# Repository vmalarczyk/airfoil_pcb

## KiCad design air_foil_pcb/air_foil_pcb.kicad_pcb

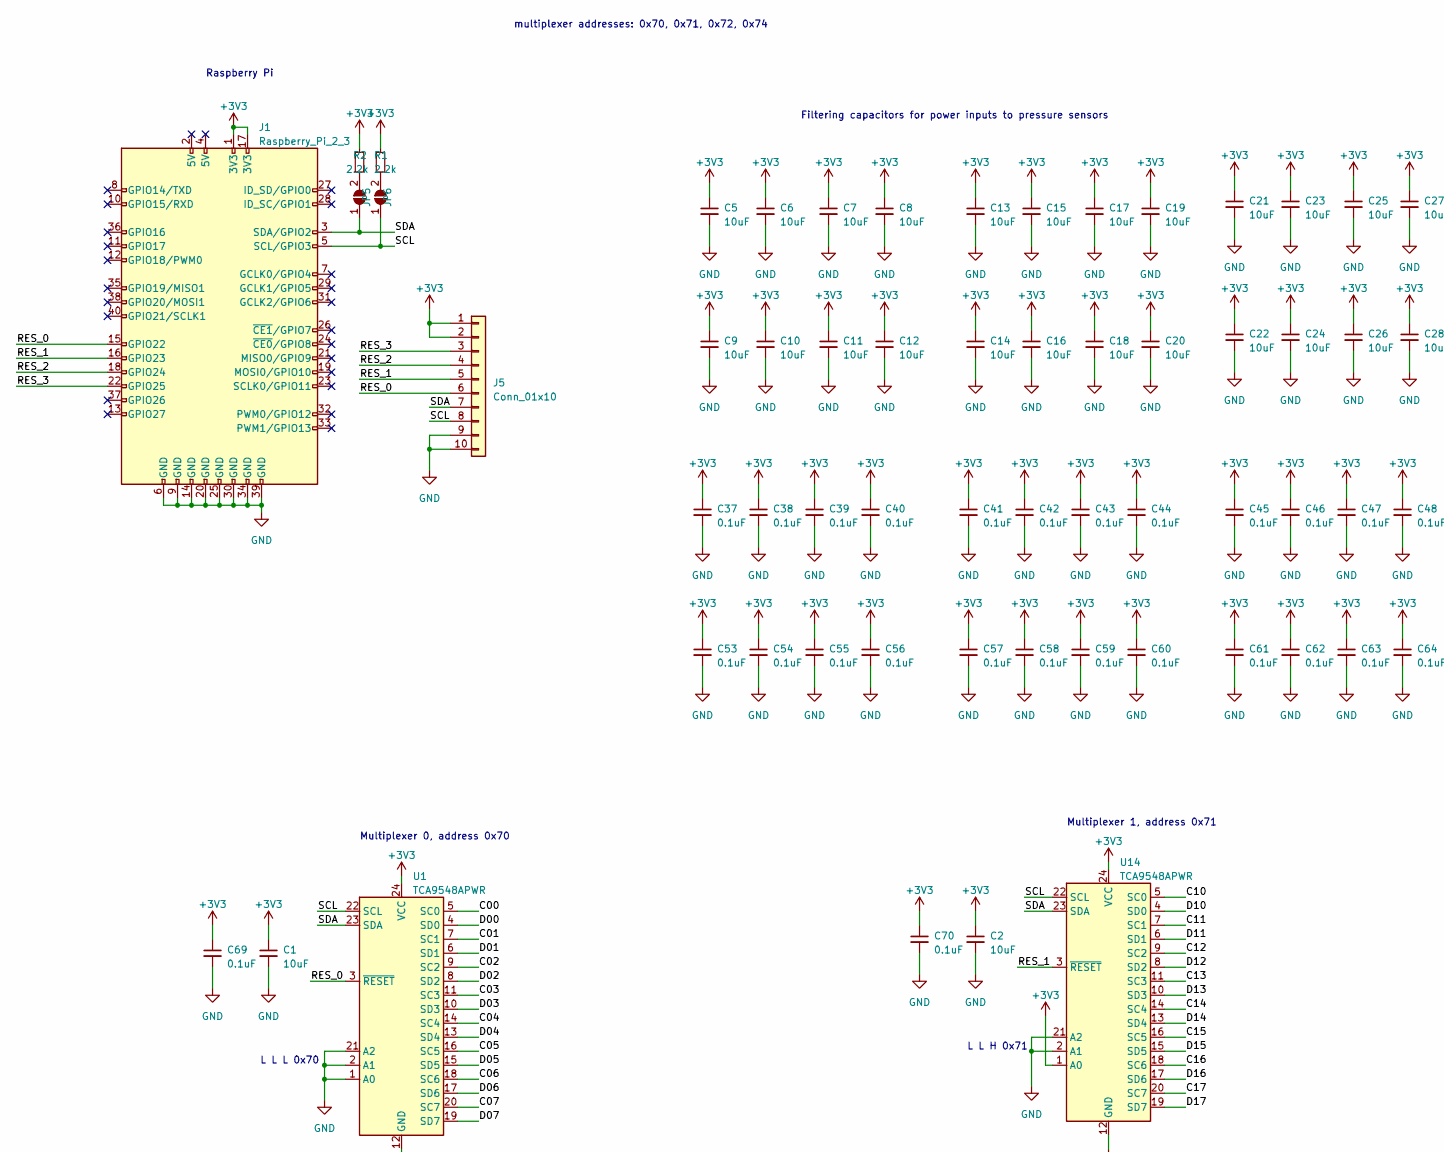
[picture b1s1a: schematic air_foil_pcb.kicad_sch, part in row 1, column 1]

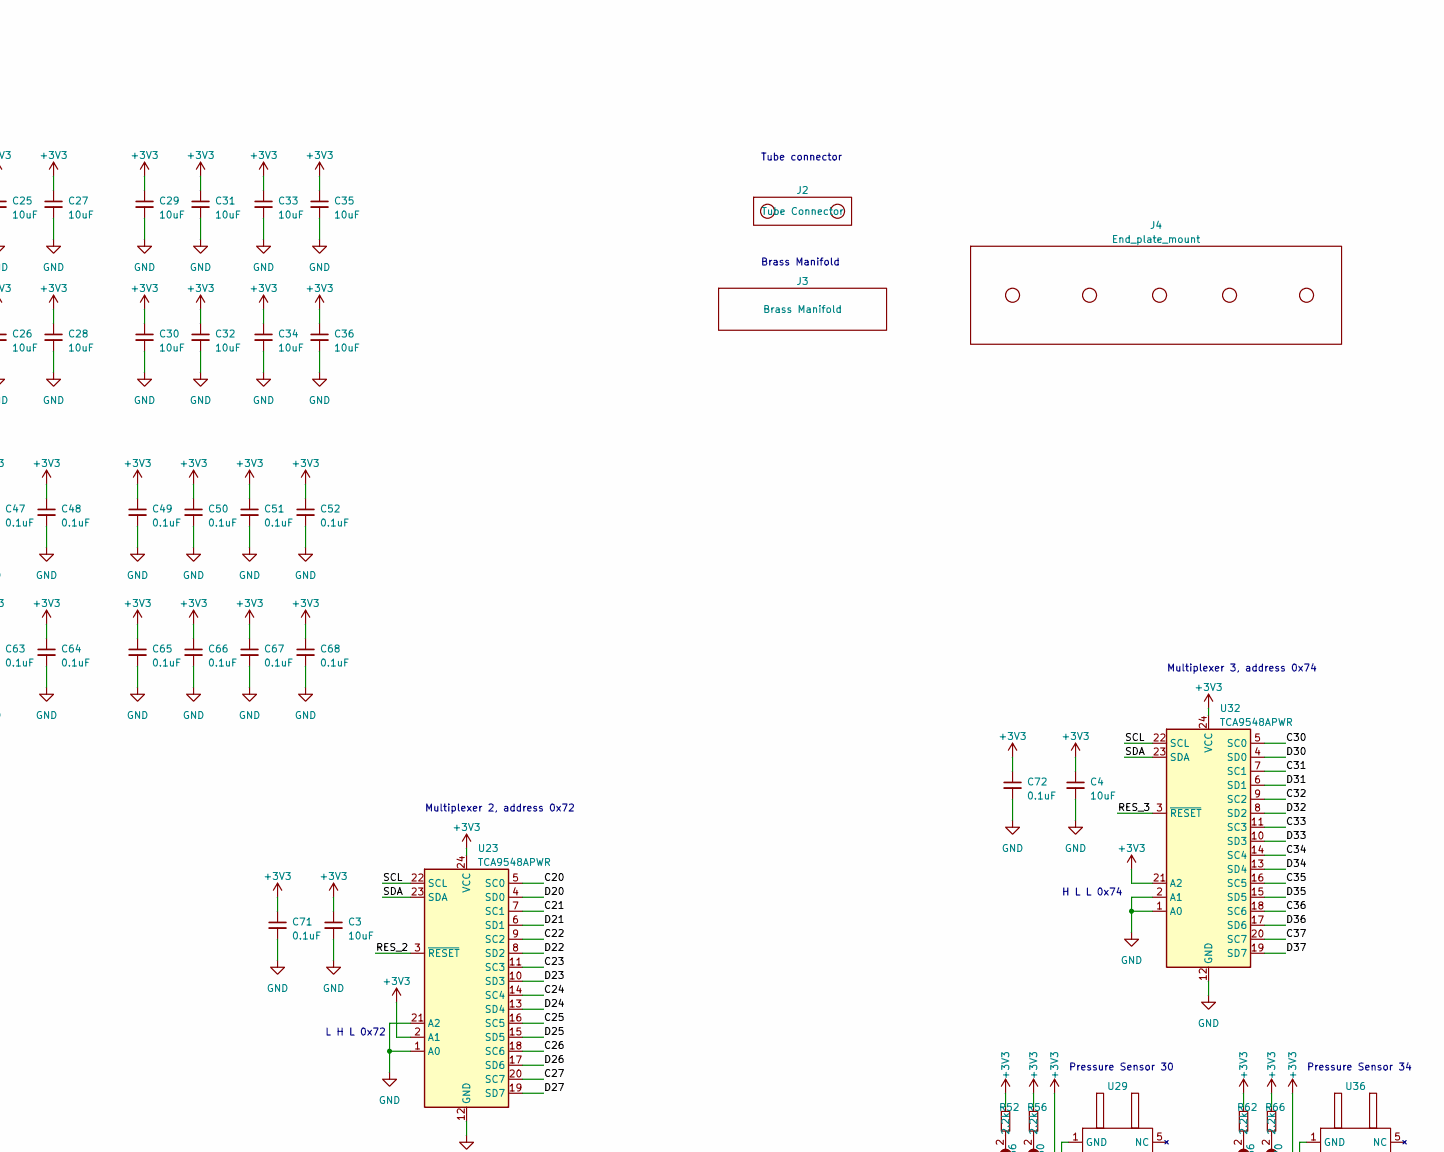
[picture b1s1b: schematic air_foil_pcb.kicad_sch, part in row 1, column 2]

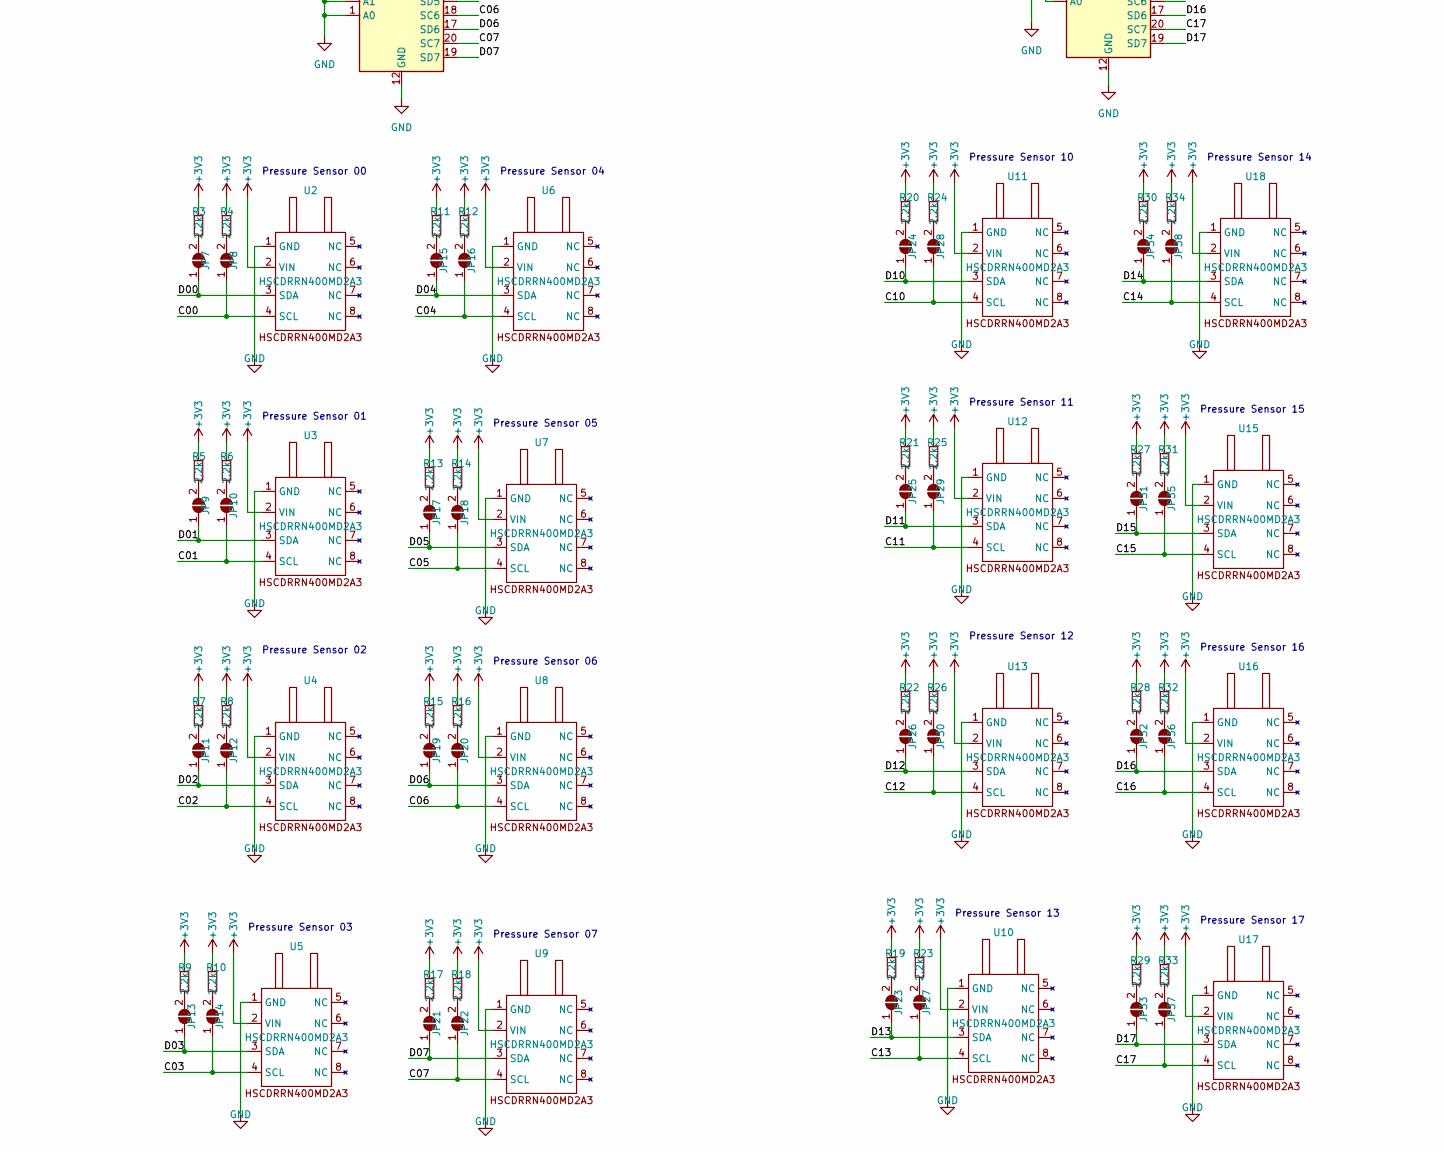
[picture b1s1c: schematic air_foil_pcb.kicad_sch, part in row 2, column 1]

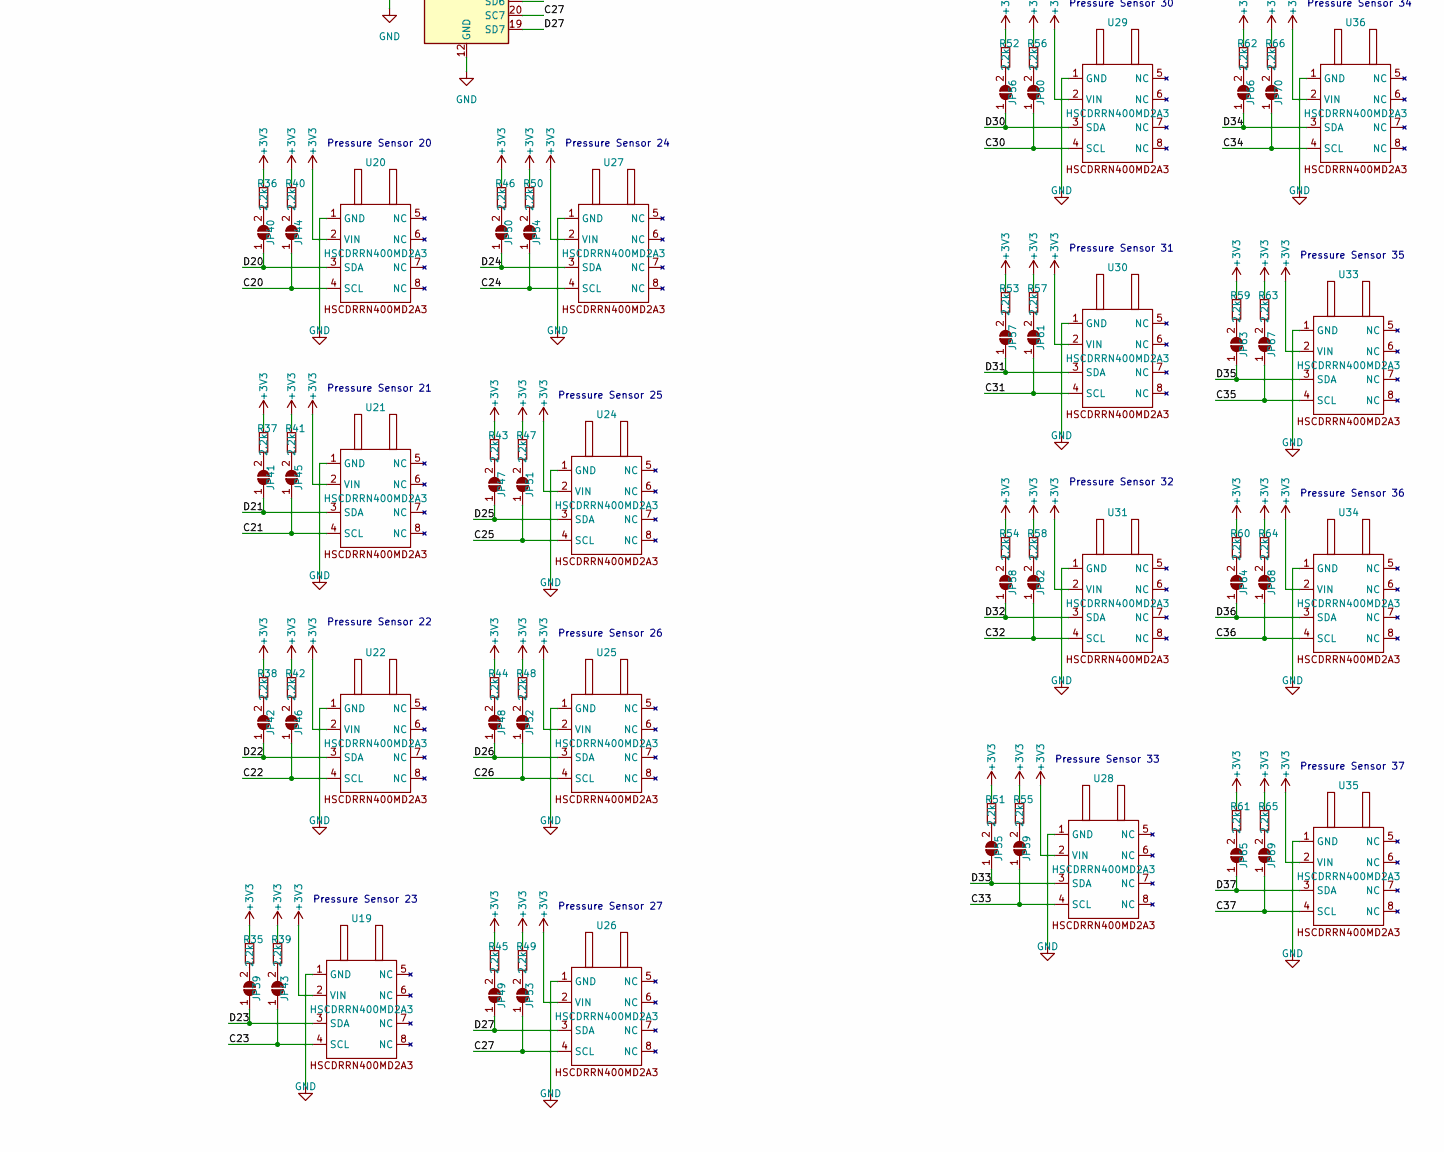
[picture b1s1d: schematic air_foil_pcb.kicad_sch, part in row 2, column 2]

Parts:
C1, C2, C3, C4, C5, C6, C7, C8, C9, C10, C11, C12, C13, C14, C15, C16, C17, C18, C19, C20, C21, C22, C23, C24, C25, C26, C27, C28, C29, C30, C31, C32, C33, C34, C35, C36: 10uF; C_0201_0603Metric; JLCPCB_Part_num C96446
C37, C38, C39, C40, C41, C42, C43, C44, C45, C46, C47, C48, C49, C50, C51, C52, C53, C54, C55, C56, C57, C58, C59, C60, C61, C62, C63, C64, C65, C66, C67, C68, C69, C70, C71, C72: 0.1uF; C_0201_0603Metric; JLCPCB_Part_num C14663
J1: Raspberry_Pi_2_3
J2: Tube Connector; tube_connector
J3: Brass Manifold; static_pressure_manifold
J4: End_plate_mount; end_plate_connector
J5: Conn_01x10; PinHeader_1x10_P2.54mm_Horizontal; JLCPCB_Part_num C86750
JP5, JP6, JP7, JP8, JP9, JP10, JP11, JP12, JP13, JP14, JP15, JP16, JP17, JP18, JP19, JP20, JP21, JP22, JP23, JP24, JP25, JP26, JP27, JP28, JP29, JP30, JP31, JP32, JP33, JP34, JP35, JP36, JP37, JP38, JP39, JP40, JP41, JP42, JP43, JP44, JP45, JP46, JP47, JP48, JP49, JP50, JP51, JP52, JP53, JP54, JP55, JP56, JP57, JP58, JP59, JP60, JP61, JP62, JP63, JP64, JP65, JP66, JP67, JP68, JP69, JP70: SolderJumper_2_Open; SolderJumper-2_P1.3mm_Open_TrianglePad1.0x1.5mm
R1, R2, R3, R4, R5, R6, R7, R8, R9, R10, R11, R12, R13, R14, R15, R16, R17, R18, R19, R20, R21, R22, R23, R24, R25, R26, R27, R28, R29, R30, R31, R32, R33, R34, R35, R36, R37, R38, R39, R40, R41, R42, R43, R44, R45, R46, R47, R48, R49, R50, R51, R52, R53, R54, R55, R56, R57, R58, R59, R60, R61, R62, R63, R64, R65, R66: 2.2k; R_01005_0402Metric; JLCPCB_Part_num C25879
U1, U14, U23, U32: TCA9548APWR; TSSOP-24_4.4x7.8mm_P0.65mm; JLCPCB_Part_num C130026
U2, U3, U4, U5, U6, U7, U8, U9, U10, U11, U12, U13, U15, U16, U17, U18, U19, U20, U21, U22, U24, U25, U26, U27, U28, U29, U30, U31, U33, U34, U35, U36: HSCDRRN400MD2A3; hscdrrn400md2a3

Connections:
+3V3: C1.1, C2.1, C3.1, C4.1, C5.1, C6.1, C7.1, C8.1, C9.1, C10.1, C11.1, C12.1, C13.1, C14.1, C15.1, C16.1, C17.1, C18.1, C19.1, C20.1, C21.1, C22.1, C23.1, C24.1, C25.1, C26.1, C27.1, C28.1, C29.1, C30.1, C31.1, C32.1, C33.1, C34.1, C35.1, C36.1, C37.1, C38.1, C39.1, C40.1, C41.1, C42.1, C43.1, C44.1, C45.1, C46.1, C47.1, C48.1, C49.1, C50.1, C51.1, C52.1, C53.1, C54.1, C55.1, C56.1, C57.1, C58.1, C59.1, C60.1, C61.1, C62.1, C63.1, C64.1, C65.1, C66.1, C67.1, C68.1, C69.1, C70.1, C71.1, C72.1, J1.1 (3V3), J1.17 (3V3), J5.1, J5.2, R1.1, R2.1, R3.1, R4.1, R5.1, R6.1, R7.1, R8.1, R9.1, R10.1, R11.1, R12.1, R13.1, R14.1, R15.1, R16.1, R17.1, R18.1, R19.1, R20.1, R21.1, R22.1, R23.1, R24.1, R25.1, R26.1, R27.1, R28.1, R29.1, R30.1, R31.1, R32.1, R33.1, R34.1, R35.1, R36.1, R37.1, R38.1, R39.1, R40.1, R41.1, R42.1, R43.1, R44.1, R45.1, R46.1, R47.1, R48.1, R49.1, R50.1, R51.1, R52.1, R53.1, R54.1, R55.1, R56.1, R57.1, R58.1, R59.1, R60.1, R61.1, R62.1, R63.1, R64.1, R65.1, R66.1, U1.24 (VCC), U2.2 (VIN), U3.2 (VIN), U4.2 (VIN), U5.2 (VIN), U6.2 (VIN), U7.2 (VIN), U8.2 (VIN), U9.2 (VIN), U10.2 (VIN), U11.2 (VIN), U12.2 (VIN), U13.2 (VIN), U14.1 (A0), U14.24 (VCC), U15.2 (VIN), U16.2 (VIN), U17.2 (VIN), U18.2 (VIN), U19.2 (VIN), U20.2 (VIN), U21.2 (VIN), U22.2 (VIN), U23.2 (A1), U23.24 (VCC), U24.2 (VIN), U25.2 (VIN), U26.2 (VIN), U27.2 (VIN), U28.2 (VIN), U29.2 (VIN), U30.2 (VIN), U31.2 (VIN), U32.21 (A2), U32.24 (VCC), U33.2 (VIN), U34.2 (VIN), U35.2 (VIN), U36.2 (VIN)
/C00: JP8.1 (A), U1.5 (SC0), U2.4 (SCL)
/C01: JP10.1 (A), U1.7 (SC1), U3.4 (SCL)
/C02: JP12.1 (A), U1.9 (SC2), U4.4 (SCL)
/C03: JP14.1 (A), U1.11 (SC3), U5.4 (SCL)
/C04: JP16.1 (A), U1.14 (SC4), U6.4 (SCL)
/C05: JP18.1 (A), U1.16 (SC5), U7.4 (SCL)
/C06: JP20.1 (A), U1.18 (SC6), U8.4 (SCL)
/C07: JP22.1 (A), U1.20 (SC7), U9.4 (SCL)
/C10: JP28.1 (A), U11.4 (SCL), U14.5 (SC0)
/C11: JP29.1 (A), U12.4 (SCL), U14.7 (SC1)
/C12: JP30.1 (A), U13.4 (SCL), U14.9 (SC2)
/C13: JP27.1 (A), U10.4 (SCL), U14.11 (SC3)
/C14: JP38.1 (A), U14.14 (SC4), U18.4 (SCL)
/C15: JP35.1 (A), U14.16 (SC5), U15.4 (SCL)
/C16: JP36.1 (A), U14.18 (SC6), U16.4 (SCL)
/C17: JP37.1 (A), U14.20 (SC7), U17.4 (SCL)
/C20: JP44.1 (A), U20.4 (SCL), U23.5 (SC0)
/C21: JP45.1 (A), U21.4 (SCL), U23.7 (SC1)
/C22: JP46.1 (A), U22.4 (SCL), U23.9 (SC2)
/C23: JP43.1 (A), U19.4 (SCL), U23.11 (SC3)
/C24: JP54.1 (A), U23.14 (SC4), U27.4 (SCL)
/C25: JP51.1 (A), U23.16 (SC5), U24.4 (SCL)
/C26: JP52.1 (A), U23.18 (SC6), U25.4 (SCL)
/C27: JP53.1 (A), U23.20 (SC7), U26.4 (SCL)
/C30: JP60.1 (A), U29.4 (SCL), U32.5 (SC0)
/C31: JP61.1 (A), U30.4 (SCL), U32.7 (SC1)
/C32: JP62.1 (A), U31.4 (SCL), U32.9 (SC2)
/C33: JP59.1 (A), U28.4 (SCL), U32.11 (SC3)
/C34: JP70.1 (A), U32.14 (SC4), U36.4 (SCL)
/C35: JP67.1 (A), U32.16 (SC5), U33.4 (SCL)
/C36: JP68.1 (A), U32.18 (SC6), U34.4 (SCL)
/C37: JP69.1 (A), U32.20 (SC7), U35.4 (SCL)
/D00: JP7.1 (A), U1.4 (SD0), U2.3 (SDA)
/D01: JP9.1 (A), U1.6 (SD1), U3.3 (SDA)
/D02: JP11.1 (A), U1.8 (SD2), U4.3 (SDA)
/D03: JP13.1 (A), U1.10 (SD3), U5.3 (SDA)
/D04: JP15.1 (A), U1.13 (SD4), U6.3 (SDA)
/D05: JP17.1 (A), U1.15 (SD5), U7.3 (SDA)
/D06: JP19.1 (A), U1.17 (SD6), U8.3 (SDA)
/D07: JP21.1 (A), U1.19 (SD7), U9.3 (SDA)
/D10: JP24.1 (A), U11.3 (SDA), U14.4 (SD0)
/D11: JP25.1 (A), U12.3 (SDA), U14.6 (SD1)
/D12: JP26.1 (A), U13.3 (SDA), U14.8 (SD2)
/D13: JP23.1 (A), U10.3 (SDA), U14.10 (SD3)
/D14: JP34.1 (A), U14.13 (SD4), U18.3 (SDA)
/D15: JP31.1 (A), U14.15 (SD5), U15.3 (SDA)
/D16: JP32.1 (A), U14.17 (SD6), U16.3 (SDA)
/D17: JP33.1 (A), U14.19 (SD7), U17.3 (SDA)
/D20: JP40.1 (A), U20.3 (SDA), U23.4 (SD0)
/D21: JP41.1 (A), U21.3 (SDA), U23.6 (SD1)
/D22: JP42.1 (A), U22.3 (SDA), U23.8 (SD2)
/D23: JP39.1 (A), U19.3 (SDA), U23.10 (SD3)
/D24: JP50.1 (A), U23.13 (SD4), U27.3 (SDA)
/D25: JP47.1 (A), U23.15 (SD5), U24.3 (SDA)
/D26: JP48.1 (A), U23.17 (SD6), U25.3 (SDA)
/D27: JP49.1 (A), U23.19 (SD7), U26.3 (SDA)
/D30: JP56.1 (A), U29.3 (SDA), U32.4 (SD0)
/D31: JP57.1 (A), U30.3 (SDA), U32.6 (SD1)
/D32: JP58.1 (A), U31.3 (SDA), U32.8 (SD2)
/D33: JP55.1 (A), U28.3 (SDA), U32.10 (SD3)
/D34: JP66.1 (A), U32.13 (SD4), U36.3 (SDA)
/D35: JP63.1 (A), U32.15 (SD5), U33.3 (SDA)
/D36: JP64.1 (A), U32.17 (SD6), U34.3 (SDA)
/D37: JP65.1 (A), U32.19 (SD7), U35.3 (SDA)
/RES_0: J1.15 (GPIO22), J5.6, U1.3 (~RESET)
/RES_1: J1.16 (GPIO23), J5.5, U14.3 (~RESET)
/RES_2: J1.18 (GPIO24), J5.4, U23.3 (~RESET)
/RES_3: J1.22 (GPIO25), J5.3, U32.3 (~RESET)
/SCL: J1.5 (SCL/GPIO3), J5.8, JP6.1 (A), U1.22 (SCL), U14.22 (SCL), U23.22 (SCL), U32.22 (SCL)
/SDA: J1.3 (SDA/GPIO2), J5.7, JP5.1 (A), U1.23 (SDA), U14.23 (SDA), U23.23 (SDA), U32.23 (SDA)
GND: C1.2, C2.2, C3.2, C4.2, C5.2, C6.2, C7.2, C8.2, C9.2, C10.2, C11.2, C12.2, C13.2, C14.2, C15.2, C16.2, C17.2, C18.2, C19.2, C20.2, C21.2, C22.2, C23.2, C24.2, C25.2, C26.2, C27.2, C28.2, C29.2, C30.2, C31.2, C32.2, C33.2, C34.2, C35.2, C36.2, C37.2, C38.2, C39.2, C40.2, C41.2, C42.2, C43.2, C44.2, C45.2, C46.2, C47.2, C48.2, C49.2, C50.2, C51.2, C52.2, C53.2, C54.2, C55.2, C56.2, C57.2, C58.2, C59.2, C60.2, C61.2, C62.2, C63.2, C64.2, C65.2, C66.2, C67.2, C68.2, C69.2, C70.2, C71.2, C72.2, J1.6 (GND), J1.9 (GND), J1.14 (GND), J1.20 (GND), J1.25 (GND), J1.30 (GND), J1.34 (GND), J1.39 (GND), J5.9, J5.10, U1.1 (A0), U1.2 (A1), U1.12 (GND), U1.21 (A2), U2.1 (GND), U3.1 (GND), U4.1 (GND), U5.1 (GND), U6.1 (GND), U7.1 (GND), U8.1 (GND), U9.1 (GND), U10.1 (GND), U11.1 (GND), U12.1 (GND), U13.1 (GND), U14.2 (A1), U14.12 (GND), U14.21 (A2), U15.1 (GND), U16.1 (GND), U17.1 (GND), U18.1 (GND), U19.1 (GND), U20.1 (GND), U21.1 (GND), U22.1 (GND), U23.1 (A0), U23.12 (GND), U23.21 (A2), U24.1 (GND), U25.1 (GND), U26.1 (GND), U27.1 (GND), U28.1 (GND), U29.1 (GND), U30.1 (GND), U31.1 (GND), U32.1 (A0), U32.2 (A1), U32.12 (GND), U33.1 (GND), U34.1 (GND), U35.1 (GND), U36.1 (GND)
unnamed: JP5.2 (B), R2.2
unnamed: JP6.2 (B), R1.2
unnamed: JP7.2 (B), R3.2
unnamed: JP8.2 (B), R4.2
unnamed: JP9.2 (B), R5.2
unnamed: JP10.2 (B), R6.2
unnamed: JP11.2 (B), R7.2
unnamed: JP12.2 (B), R8.2
unnamed: JP13.2 (B), R9.2
unnamed: JP14.2 (B), R10.2
unnamed: JP15.2 (B), R11.2
unnamed: JP16.2 (B), R12.2
unnamed: JP17.2 (B), R13.2
unnamed: JP18.2 (B), R14.2
unnamed: JP19.2 (B), R15.2
unnamed: JP20.2 (B), R16.2
unnamed: JP21.2 (B), R17.2
unnamed: JP22.2 (B), R18.2
unnamed: JP23.2 (B), R19.2
unnamed: JP24.2 (B), R20.2
unnamed: JP25.2 (B), R21.2
unnamed: JP26.2 (B), R22.2
unnamed: JP27.2 (B), R23.2
unnamed: JP28.2 (B), R24.2
unnamed: JP29.2 (B), R25.2
unnamed: JP30.2 (B), R26.2
unnamed: JP31.2 (B), R27.2
unnamed: JP32.2 (B), R28.2
unnamed: JP33.2 (B), R29.2
unnamed: JP34.2 (B), R30.2
unnamed: JP35.2 (B), R31.2
unnamed: JP36.2 (B), R32.2
unnamed: JP37.2 (B), R33.2
unnamed: JP38.2 (B), R34.2
unnamed: JP39.2 (B), R35.2
unnamed: JP40.2 (B), R36.2
unnamed: JP41.2 (B), R37.2
unnamed: JP42.2 (B), R38.2
unnamed: JP43.2 (B), R39.2
unnamed: JP44.2 (B), R40.2
unnamed: JP45.2 (B), R41.2
unnamed: JP46.2 (B), R42.2
unnamed: JP47.2 (B), R43.2
unnamed: JP48.2 (B), R44.2
unnamed: JP49.2 (B), R45.2
unnamed: JP50.2 (B), R46.2
unnamed: JP51.2 (B), R47.2
unnamed: JP52.2 (B), R48.2
unnamed: JP53.2 (B), R49.2
unnamed: JP54.2 (B), R50.2
unnamed: JP55.2 (B), R51.2
unnamed: JP56.2 (B), R52.2
unnamed: JP57.2 (B), R53.2
unnamed: JP58.2 (B), R54.2
unnamed: JP59.2 (B), R55.2
unnamed: JP60.2 (B), R56.2
unnamed: JP61.2 (B), R57.2
unnamed: JP62.2 (B), R58.2
unnamed: JP63.2 (B), R59.2
unnamed: JP64.2 (B), R60.2
unnamed: JP65.2 (B), R61.2
unnamed: JP66.2 (B), R62.2
unnamed: JP67.2 (B), R63.2
unnamed: JP68.2 (B), R64.2
unnamed: JP69.2 (B), R65.2
unnamed: JP70.2 (B), R66.2

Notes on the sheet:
Multiplexer 3, address 0x74
Pressure Sensor 13
Brass Manifold
Pressure Sensor 27
Pressure Sensor 32
L H L 0x72
Pressure Sensor 04
multiplexer addresses: 0x70, 0x71, 0x72, 0x74
Pressure Sensor 24
H L L 0x74
Pressure Sensor 07
Pressure Sensor 15
Pressure Sensor 06
Pressure Sensor 25
Pressure Sensor 23
Pressure Sensor 33
Filtering capacitors for power inputs to pressure sensors
Tube connector
Pressure Sensor 11
Pressure Sensor 20
Pressure Sensor 31
Pressure Sensor 03
Pressure Sensor 00
Pressure Sensor 01
Pressure Sensor 10
Raspberry Pi
Pressure Sensor 16
Pressure Sensor 14
Pressure Sensor 36
Pressure Sensor 12
Pressure Sensor 30
L L L 0x70
Pressure Sensor 34
Pressure Sensor 05
Pressure Sensor 37
Multiplexer 1, address 0x71
Pressure Sensor 22
L L H 0x71
Pressure Sensor 35
Multiplexer 2, address 0x72

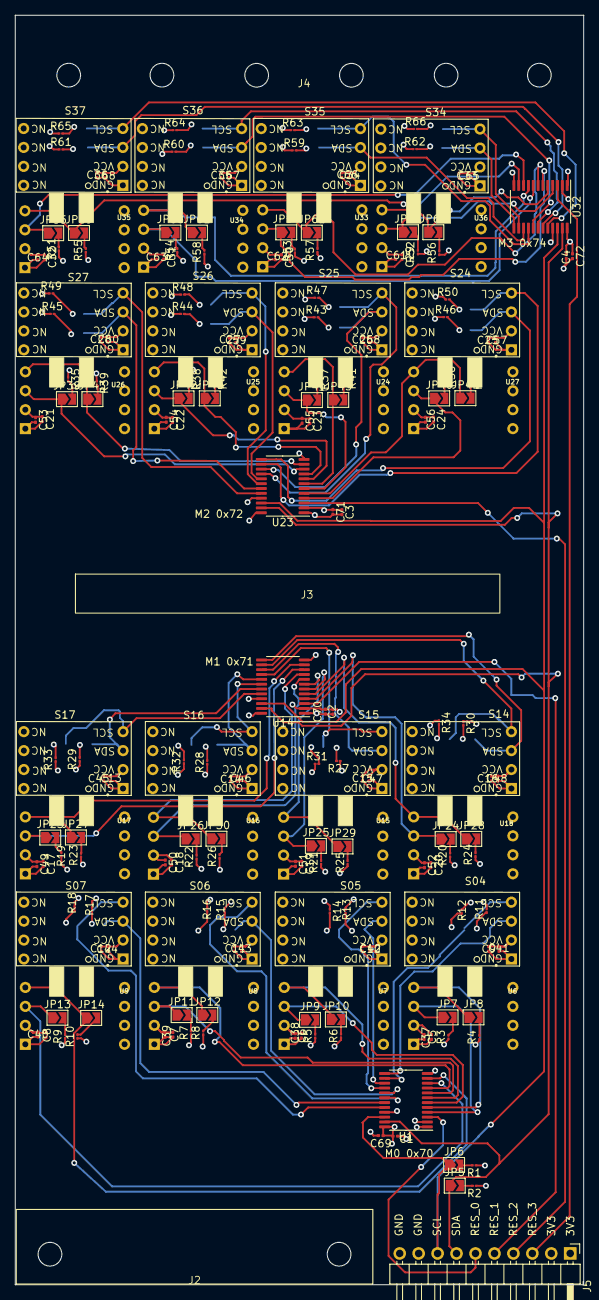
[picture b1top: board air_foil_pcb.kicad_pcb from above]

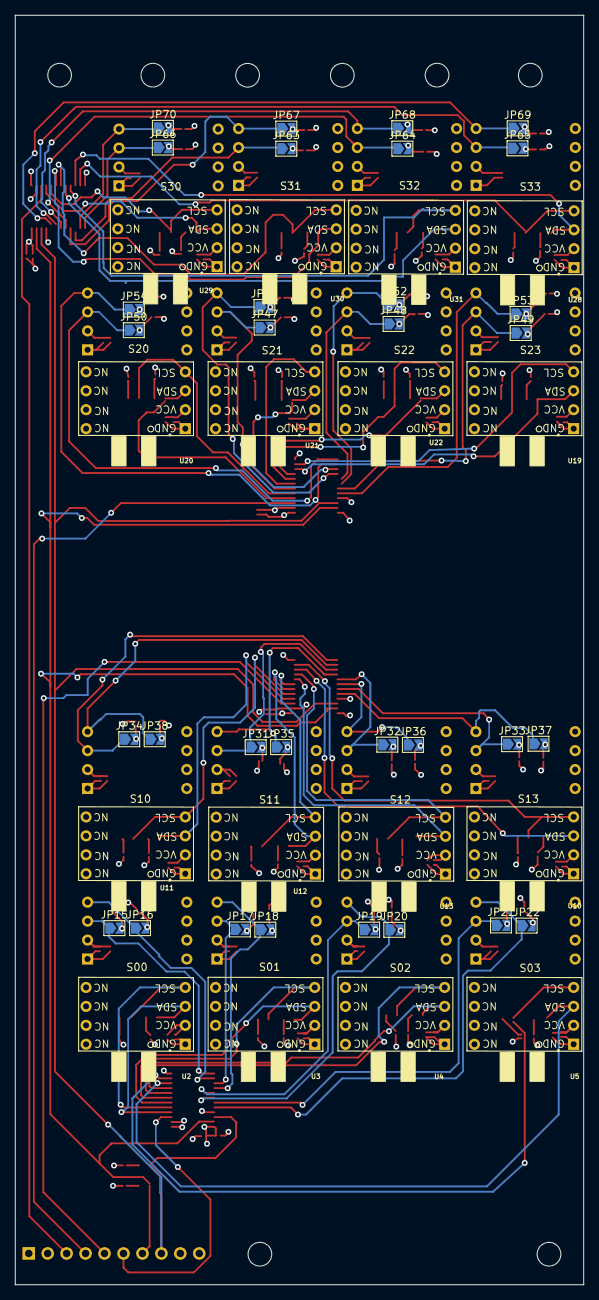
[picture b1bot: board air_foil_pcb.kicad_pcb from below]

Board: 4 copper layers, 76.2 x 170.2 mm, 244 parts (48 on the bottom side), 138 nets.

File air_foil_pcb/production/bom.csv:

Designator,Footprint,Quantity,Value,LCSC Part #
"C1, C10, C11, C12, C13, C14, C15, C16, C17, C18, C19, C2, C20, C21, C22, C23, C24, C25, C26, C27, C28, C29, C3, C30, C31, C32, C33, C34, C35, C36, C4, C5, C6, C7, C8, C9",0201,36,10uF,C96446
"C37, C38, C39, C40, C41, C42, C43, C44, C45, C46, C47, C48, C49, C50, C51, C52, C53, C54, C55, C56, C57, C58, C59, C60, C61, C62, C63, C64, C65, C66, C67, C68, C69, C70, C71, C72",0201,36,0.1uF,C14663
J2,tube_connector,1,Tube Connector,
J3,static_pressure_manifold,1,Brass Manifold,
J4,end_plate_connector,1,End_plate_mount,
J5,PinHeader_1x10_P2.54mm_Horizontal,1,Conn_01x10,C86750
"JP10, JP11, JP12, JP13, JP14, JP15, JP16, JP17, JP18, JP19, JP20, JP21, JP22, JP23, JP24, JP25, JP26, JP27, JP28, JP29, JP30, JP31, JP32, JP33, JP34, JP35, JP36, JP37, JP38, JP39, JP40, JP41, JP42, JP43, JP44, JP45, JP46, JP47, JP48, JP49, JP5, JP50, JP51, JP52, JP53, JP54, JP55, JP56, JP57, JP58, JP59, JP6, JP60, JP61, JP62, JP63, JP64, JP65, JP66, JP67, JP68, JP69, JP7, JP70, JP8, JP9",SolderJumper-2_P1.3mm_Open_TrianglePad1.0x1.5mm,66,SolderJumper_2_Open,
"R1, R10, R11, R12, R13, R14, R15, R16, R17, R18, R19, R2, R20, R21, R22, R23, R24, R25, R26, R27, R28, R29, R3, R30, R31, R32, R33, R34, R35, R36, R37, R38, R39, R4, R40, R41, R42, R43, R44, R45, R46, R47, R48, R49, R5, R50, R51, R52, R53, R54, R55, R56, R57, R58, R59, R6, R60, R61, R62, R63, R64, R65, R66, R7, R8, R9",01005,66,2.2k,C25879
"U1, U14, U23, U32",TSSOP-24_4.4x7.8mm_P0.65mm,4,TCA9548APWR,C130026
"U10, U11, U12, U13, U15, U16, U17, U18, U19, U2, U20, U21, U22, U24, U25, U26, U27, U28, U29, U3, U30, U31, U33, U34, U35, U36, U4, U5, U6, U7, U8, U9",hscdrrn400md2a3,32,HSCDRRN400MD2A3,

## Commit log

2024-07-06 created schematic for HSC pressure sensor, started work on main schematic
2024-07-07 made adjustment to pressure sensor schematic, schematic for first multiplexer and associated sensor completed
2024-07-07 finished schematic, added tube connector
2024-07-07 added 0.1uF caps to power inputs for high frequency filtering
2024-07-12 working on schematic
2024-07-12 finished layout
2024-07-13 fab files created
2024-07-13 added jlcpcb production folder, modified rotations for production file
